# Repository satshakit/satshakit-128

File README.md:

<h1 style="font-family: courier;" align="center"> satshakit 128</h1>
<p align="center">

<div align="center"><i>An improved & fabbable Arduino IDE/libraries compatible board.</i></div>
</p>  

What is satshakit?
--

satshakit is a **Arduino IDE  and libraries compatible**, fabbable and open source board, and also an improved version of [Fabkit](http://fabacademy.org/archives/2015/doc/projects/fabkit-0.4.html). 

Here you can find all of the satshakit boards: **[satshakit organization](https://github.com/satshakit)**.

satshakit 128
--

**satshakit 128** is microcontroller board designed around the **ATMega1284P** chip and it is suitable for complex scenarios in which is needed to have more flash and ram memory, but also the possibility to use 2 serial simultaneously.

In comparison with the other satshakits based on ATMega328P satshakit 128 has:

- **128k** flash memory instead of 32k
- **2 serials** instead of 1
- **16k of ram** instead of 2k
- **32 IO** pins instead of 23

Finally satshakit 128 is smaller than satshakit cnc and it costs **13 euro** each (much less for more).

Here you can have a look on **satshakit 128 board**:

**downloads (right click, download as)**

- [satshakit 128 svg](https://raw.githubusercontent.com/satshakit/satshakit-128/master/media/satshakit128.svg)
- [satshakit 128 internal png](https://raw.githubusercontent.com/satshakit/satshakit-128/master/media/satshakit128_internal.png)
- [satshakit 128 cut png](https://raw.githubusercontent.com/satshakit/satshakit-128/master/media/satshakit128_cut.png)
- [satshakit 128 schematic](https://raw.githubusercontent.com/satshakit/satshakit-128/master/eagle/satshakit128/satshakit128.sch)
- [satshakit 128 board](https://github.com/satshakit/satshakit-128/raw/master/eagle/satshakit128/satshakit128.brd)
- [satshakit 128 BOM Open Document](https://github.com/satshakit/satshakit-128/raw/master/docs/satshakit_128.ods)
- [satshakit 128 BOM Excel](https://github.com/satshakit/satshakit-128/raw/master/docs/satshakit_128.xlsx)

**media**

satshakit 128 uploading bootloader:

satshakit 128 uploading blink:

Getting Started
--
A satshakit board is **very similar to an Arduino board**, thus is possible to use the Arduino IDE and its libraries. When you finish solder satshakit 128, you have to program it. If you want to use satshakit as an Arduino, you first need to **upload Arduino bootloader**. This will also set the ATmega1284P fuses. Before doing any programming you need to **patch your arduino IDE** using a specific set of files that will add the satshakit 128 as an available board to use. 

To add the support for satshakit 128 you can use the **[Mighty 1284P](https://github.com/JChristensen/mighty-1284p/tree/v1.6.3)**, that is provided in this repo inside the **[mighty-1284p folder](https://github.com/satshakit/satshakit-128/tree/master/mighty-1284p)**. 

To do so follow these steps:

1. **download** satshakit 128 repository
2. close **Arduino IDE** before doing anything
3. copy the folder named **mighty-1284p** inside the **Arduino IDE hardware folder**, **arduino-1.6.x/hardware/** in Linux, **Documents/Arduino/hardware** in MacOS 
4. open again the Arduino IDE
5. select **avr-developers.com pinouts 16MHz using Optiboot** board

Now you can use an Arduino as ISP to burn the bootloader and any Arduino sketch you want. To upload a program you connect **Arduino to the satshakit 128** as follows:

Once everything is connected, follow these steps to upload Arduino bootloader:

1. open Arduino IDE 
2. select proper programmer Arduino as ISP
3. select **avr-developers.com pinouts 16MHz using Optiboot** board
4. click on tools->Burn Bootloader

After you burnt the bootloader you can also use an **FTDI usb cable** to program the satshakit 128. Here is the connection schema to program the satshakit 128 using an FTDI cable:

Remember that if you try to program the satshakit 128 using an Arduino, then you will also delete the bootloader, losing the capability to be programmed using the FTDI cable. To hae back this possibility burn again the bootloader.

Here is the Arduino pinout of the satshakit 128:

What's in the repo
--
- **[docs](https://github.com/satshakit/satshakit-128/tree/master/docs)**: BOM files for Farnell
- **[egle projects](https://github.com/satshakit/satshakit-128/tree/master/eagle/satshakit128)**: eagle projects of satshakit
- **[media](https://github.com/satshakit/satshakit-128/tree/master/media)**: svg of satshakits, connections schemas, images for cnc milling machine and fiber laser cutter, other images

Authors
--

- Daniele Ingrassia

Contact
--

- **ingrassiada@gmail.com**
- **[linkedin](http://it.linkedin.com/in/danieleingrassia)**

Thanks
--

[Fablab Kamp-Lintfort](http://fablab.hochschule-rhein-waal.de/index.php/de/)<br />
Hochschule Rhein-Waal<br />
Friedrich-Heinrich-Allee 25, 47475 Kamp-Lintfort, Germany<br />
fablab@hochschule-rhein-waal.de

[Mighty 1284P](https://github.com/JChristensen/mighty-1284p/tree/v1.6.3)

License
--
This work is licensed under the terms of the open source license: Creative Commons Attribution-ShareAlike 4.0 International ([CC BY-SA 4.0](https://creativecommons.org/licenses/by-sa/4.0/)).

Disclaimer  
--

<div class="align-justify">
This hardware/software is provided "as is", and you use the hardware/software at your own risk. Under no circumstances shall any author be liable for direct, indirect, special, incidental, or consequential damages resulting from the use, misuse, or inability to use this hardware/software, even if the authors have been advised of the possibility of such damages.</div>

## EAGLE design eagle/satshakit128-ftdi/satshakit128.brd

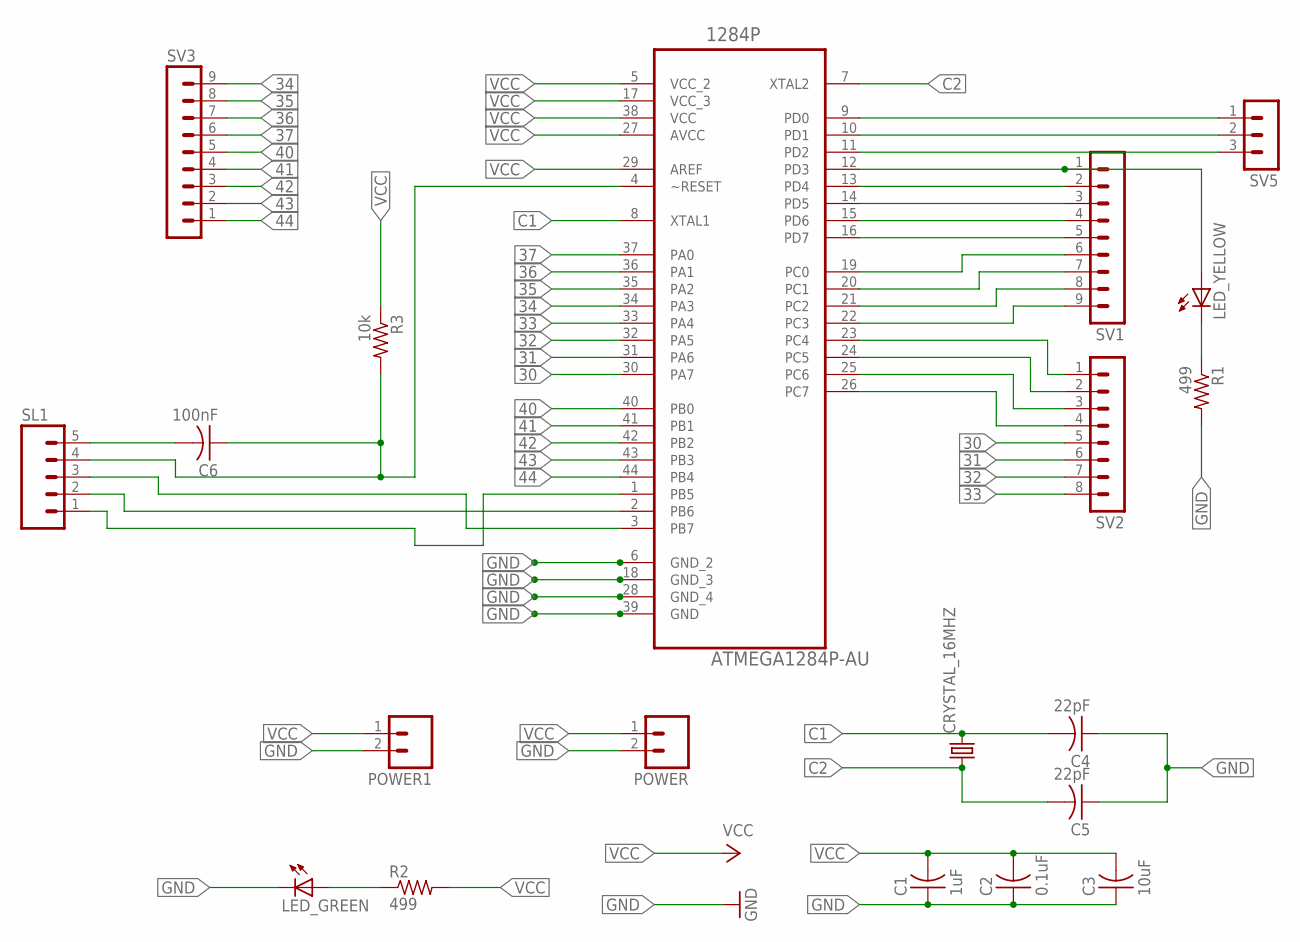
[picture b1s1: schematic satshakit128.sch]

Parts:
1284P: ATMEGA1284P-AU; QFP80P1200X1200X120-44N
C1: 1uF; C1206
C2: 0.1uF; C1206
C3: 10uF; C1206
C4, C5: 22pF; C1206
C6: 100nF; C1206
CRYSTAL_16MHZ: CRYSTALHC49UP; HC49UP
LED_GREEN: LED1206; 1206
LED_YELLOW: LED1206; 1206
POWER, POWER1: M02; 02P
R1, R2: 499; R1206
R3: 10k; R1206
SL1: M05; 05P
SV1, SV3: MA09-1
SV2: MA08-1
SV5: MA03-1

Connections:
30: 1284P.30 (PA7), SV2.5
31: 1284P.31 (PA6), SV2.6
32: 1284P.32 (PA5), SV2.7
33: 1284P.33 (PA4), SV2.8
34: 1284P.34 (PA3), SV3.9
35: 1284P.35 (PA2), SV3.8
36: 1284P.36 (PA1), SV3.7
37: 1284P.37 (PA0), SV3.6
40: 1284P.40 (PB0), SV3.5
41: 1284P.41 (PB1), SV3.4
42: 1284P.42 (PB2), SV3.3
43: 1284P.43 (PB3), SV3.2
44: 1284P.44 (PB4), SV3.1
C1: 1284P.8 (XTAL1), C4.2, CRYSTAL_16MHZ.2
C2: 1284P.7 (XTAL2), C5.2, CRYSTAL_16MHZ.1
GND: 1284P.6 (GND_2), C1.1, C2.1, C3.1, C4.1, C5.1, LED_GREEN.2 (C), POWER.2, POWER1.2, R1.2
unnamed: 1284P.19 (PC0), SV1.6
unnamed: 1284P.20 (PC1), SV1.7
unnamed: 1284P.16 (PD7), SV1.5
unnamed: 1284P.14 (PD5), SV1.3
unnamed: 1284P.13 (PD4), SV1.2
unnamed: 1284P.12 (PD3), LED_YELLOW.1 (A), SV1.1
unnamed: 1284P.11 (PD2), SV5.3
unnamed: 1284P.10 (PD1), SV5.2
unnamed: 1284P.9 (PD0), SV5.1
unnamed: 1284P.21 (PC2), SV1.8
unnamed: 1284P.22 (PC3), SV1.9
unnamed: 1284P.23 (PC4), SV2.1
unnamed: 1284P.24 (PC5), SV2.2
unnamed: 1284P.25 (PC6), SV2.3
unnamed: 1284P.26 (PC7), SV2.4
unnamed: 1284P.15 (PD6), SV1.4
unnamed: 1284P.3 (PB7), SL1.3
unnamed: 1284P.2 (PB6), SL1.2
unnamed: 1284P.1 (PB5), SL1.1
unnamed: 1284P.4 (~RESET), C6.1, R3.2, SL1.4
unnamed: LED_YELLOW.2 (C), R1.1
unnamed: LED_GREEN.1 (A), R2.1
unnamed: C6.2, SL1.5
VCC: 1284P.5 (VCC_2), 1284P.17 (VCC_3), 1284P.27 (AVCC), 1284P.29 (AREF), C1.2, C2.2, C3.2, POWER.1, POWER1.1, R2.2, R3.1

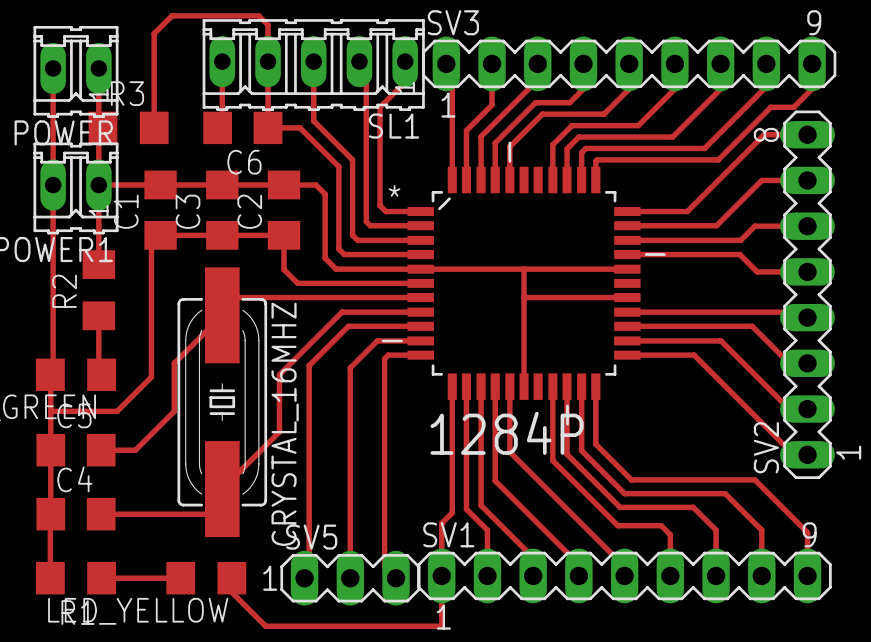
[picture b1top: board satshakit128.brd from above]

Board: 2 copper layers, 20 parts (0 on the bottom side), 40 nets.

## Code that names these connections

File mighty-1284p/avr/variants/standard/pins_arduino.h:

#ifndef Pins_Arduino_h
#define Pins_Arduino_h

#include <avr/pgmspace.h>

// ATMEL ATMEGA1284P
//
//                       +---\/---+
//           (D 0) PB0  1|        |40  PA0 (AI 0 / D24)
//           (D 1) PB1  2|        |39  PA1 (AI 1 / D25)
//      INT2 (D 2) PB2  3|        |38  PA2 (AI 2 / D26)
//       PWM (D 3) PB3  4|        |37  PA3 (AI 3 / D27)
//    PWM/SS (D 4) PB4  5|        |36  PA4 (AI 4 / D28)
//      MOSI (D 5) PB5  6|        |35  PA5 (AI 5 / D29)
//  PWM/MISO (D 6) PB6  7|        |34  PA6 (AI 6 / D30)
//   PWM/SCK (D 7) PB7  8|        |33  PA7 (AI 7 / D31)
//                 RST  9|        |32  AREF
//                 VCC 10|        |31  GND 
//                 GND 11|        |30  AVCC
//               XTAL2 12|        |29  PC7 (D 23)
//               XTAL1 13|        |28  PC6 (D 22)
//      RX0 (D 8)  PD0 14|        |27  PC5 (D 21) TDI
//      TX0 (D 9)  PD1 15|        |26  PC4 (D 20) TDO
// RX1/INT0 (D 10) PD2 16|        |25  PC3 (D 19) TMS
// TX1/INT1 (D 11) PD3 17|        |24  PC2 (D 18) TCK
//      PWM (D 12) PD4 18|        |23  PC1 (D 17) SDA
//      PWM (D 13) PD5 19|        |22  PC0 (D 16) SCL
//      PWM (D 14) PD6 20|        |21  PD7 (D 15) PWM
//                       +--------+
//

/*
   PCINT15-8: D7-0  : bit 1
   PCINT31-24: D15-8  : bit 3
   PCINT23-16: D23-16 : bit 2
   PCINT7-0: D31-24   : bit 0
   */

#define MIGHTY_1284P_VARIANT "STANDARD"

#define NUM_DIGITAL_PINS            32
#define NUM_ANALOG_INPUTS           8
#define analogInputToDigitalPin(p)  ( (p) < NUM_ANALOG_INPUTS ? (p) + 24 : -1 )
#define digitalPinToAnalogPin(p)    ( (p) >= 24 && (p) <= 31 ? (p) - 24 : -1 )
#define analogPinToChannel(p)       ( (p) < NUM_ANALOG_INPUTS ? (p) : (p) >= 24 ? (p) - 24 : -1 )    //required macro for mighty-1284p core
#define digitalPinHasPWM(p)         ( (p) == 3 || (p) == 4 || (p) == 6 || (p) == 7 || (p) == 12 || (p) == 13 || (p) == 14 || (p) == 15 )

static const uint8_t SS   = 4;
static const uint8_t MOSI = 5;
static const uint8_t MISO = 6;
static const uint8_t SCK  = 7;

static const uint8_t SDA = 17;
static const uint8_t SCL = 16;
static const uint8_t LED_BUILTIN = 7;

static const uint8_t A0 = 24;
static const uint8_t A1 = 25;
static const uint8_t A2 = 26;
static const uint8_t A3 = 27;
static const uint8_t A4 = 28;
static const uint8_t A5 = 29;
static const uint8_t A6 = 30;
static const uint8_t A7 = 31;

#define digitalPinToPCICR(p)    ( (p) >= 0 && (p) < NUM_DIGITAL_PINS ? &PCICR : (uint8_t *)0 )
#define digitalPinToPCICRbit(p) ( (p) <= 7 ? 1 : (p) <= 15 ? 3 : (p) <= 23 ? 2 : 0 )
#define digitalPinToPCMSK(p)    ( (p) <= 7 ? &PCMSK1 : (p) <= 15 ? &PCMSK3 : (p) <= 23 ? &PCMSK2 : &PCMSK0 )
#define digitalPinToPCMSKbit(p) ( (p) % 8 )
// return associated INTx number for associated/valid pins,
// otherwise NOT_AN_INTERRUPT
#define digitalPinToInterrupt(p) \
	(\
	(p) == 10 ? 0 : \
	(p) == 11 ? 1 : \
	(p) == 2 ? 2 : \
	NOT_AN_INTERRUPT)


#define PA 1
#define PB 2
#define PC 3
#define PD 4

// specify port for each pin D0-D31
#define PORT_D0 PB
#define PORT_D1 PB
#define PORT_D2 PB
#define PORT_D3 PB
#define PORT_D4 PB
#define PORT_D5 PB
#define PORT_D6 PB
#define PORT_D7 PB
#define PORT_D8 PD
#define PORT_D9 PD
#define PORT_D10 PD
#define PORT_D11 PD
#define PORT_D12 PD
#define PORT_D13 PD
#define PORT_D14 PD
#define PORT_D15 PD
#define PORT_D16 PC
#define PORT_D17 PC
#define PORT_D18 PC
#define PORT_D19 PC
#define PORT_D20 PC
#define PORT_D21 PC
#define PORT_D22 PC
#define PORT_D23 PC
#define PORT_D24 PA
#define PORT_D25 PA
#define PORT_D26 PA
#define PORT_D27 PA
#define PORT_D28 PA
#define PORT_D29 PA
#define PORT_D30 PA
#define PORT_D31 PA

// specify port bit for each pin D0-D31
#define BIT_D0 0
#define BIT_D1 1
#define BIT_D2 2
#define BIT_D3 3
#define BIT_D4 4
#define BIT_D5 5
#define BIT_D6 6
#define BIT_D7 7
#define BIT_D8 0
#define BIT_D9 1
#define BIT_D10 2
#define BIT_D11 3
#define BIT_D12 4
#define BIT_D13 5
#define BIT_D14 6
#define BIT_D15 7
#define BIT_D16 0
#define BIT_D17 1
#define BIT_D18 2
#define BIT_D19 3
#define BIT_D20 4
#define BIT_D21 5
#define BIT_D22 6
#define BIT_D23 7
#define BIT_D24 0
#define BIT_D25 1
#define BIT_D26 2
#define BIT_D27 3
#define BIT_D28 4
#define BIT_D29 5
#define BIT_D30 6
#define BIT_D31 7

// macro equivalents of PROGMEM arrays port_to_mode_PGM[] etc. below
#define PORT_TO_MODE(x) (x == 1 ? &DDRA : (x == 2 ? &DDRB : (x == 3 ? &DDRC : (x == 4 ? &DDRD : NOT_A_PORT)))) 
#define PORT_TO_OUTPUT(x) (x == 1 ? &PORTA : (x == 2 ? &PORTB : (x == 3 ? &PORTC : (x == 4 ? &PORTD : NOT_A_PORT))))
#define PORT_TO_INPUT(x) (x == 1 ? &PINA : (x == 2 ? &PINB : (x == 3 ? &PINC : (x == 4 ? &PIND : NOT_A_PORT)))) 
 
#ifdef ARDUINO_MAIN
// these arrays map port names (e.g. port B) to the
// appropriate addresses for various functions (e.g. reading
// and writing)
const uint16_t PROGMEM port_to_mode_PGM[] =
{
  NOT_A_PORT,
  (uint16_t) &DDRA,
  (uint16_t) &DDRB,
  (uint16_t) &DDRC,
  (uint16_t) &DDRD,
};

const uint16_t PROGMEM port_to_output_PGM[] =
{
  NOT_A_PORT,
  (uint16_t) &PORTA,
  (uint16_t) &PORTB,
  (uint16_t) &PORTC,
  (uint16_t) &PORTD,
};

const uint16_t PROGMEM port_to_input_PGM[] =
{
  NOT_A_PORT,
  (uint16_t) &PINA,
  (uint16_t) &PINB,
  (uint16_t) &PINC,
  (uint16_t) &PIND,
};

const uint8_t PROGMEM digital_pin_to_port_PGM[NUM_DIGITAL_PINS] =
{
  PORT_D0,
  PORT_D1,
  PORT_D2,
  PORT_D3,
  PORT_D4,
  PORT_D5,
  PORT_D6,
  PORT_D7,
  PORT_D8,
  PORT_D9,
  PORT_D10,
  PORT_D11,
  PORT_D12,
  PORT_D13,
  PORT_D14,
  PORT_D15,
  PORT_D16,
  PORT_D17,
  PORT_D18,
  PORT_D19,
  PORT_D20,
  PORT_D21,
  PORT_D22,
  PORT_D23,
  PORT_D24,
  PORT_D25,
  PORT_D26,
  PORT_D27,
  PORT_D28,
  PORT_D29,
  PORT_D30,
  PORT_D31
};

const uint8_t PROGMEM digital_pin_to_bit_mask_PGM[NUM_DIGITAL_PINS] =
{
  _BV(BIT_D0),
  _BV(BIT_D1),
  _BV(BIT_D2),
  _BV(BIT_D3),
  _BV(BIT_D4),
  _BV(BIT_D5),
  _BV(BIT_D6),
  _BV(BIT_D7),
  _BV(BIT_D8),
  _BV(BIT_D9),
  _BV(BIT_D10),
  _BV(BIT_D11),
  _BV(BIT_D12),
  _BV(BIT_D13),
  _BV(BIT_D14),
  _BV(BIT_D15),
  _BV(BIT_D16),
  _BV(BIT_D17),
  _BV(BIT_D18),
  _BV(BIT_D19),
  _BV(BIT_D20),
  _BV(BIT_D21),
  _BV(BIT_D22),
  _BV(BIT_D23),
  _BV(BIT_D24),
  _BV(BIT_D25),
  _BV(BIT_D26),
  _BV(BIT_D27),
  _BV(BIT_D28),
  _BV(BIT_D29),
  _BV(BIT_D30),
  _BV(BIT_D31)
};

const uint8_t PROGMEM digital_pin_to_timer_PGM[] =
{
  NOT_ON_TIMER, /* 0  - PB0 */
  NOT_ON_TIMER, /* 1  - PB1 */
  NOT_ON_TIMER, /* 2  - PB2 */
  TIMER0A,     	/* 3  - PB3 */
  TIMER0B, 	/* 4  - PB4 */
  NOT_ON_TIMER, /* 5  - PB5 */
  TIMER3A, 	/* 6  - PB6 */
  TIMER3B,	/* 7  - PB7 */
  NOT_ON_TIMER, /* 8  - PD0 */
  NOT_ON_TIMER, /* 9  - PD1 */
  NOT_ON_TIMER, /* 10 - PD2 */
  NOT_ON_TIMER, /* 11 - PD3 */
  TIMER1B,     	/* 12 - PD4 */
  TIMER1A,     	/* 13 - PD5 */
  TIMER2B,     	/* 14 - PD6 */
  TIMER2A,     	/* 15 - PD7 */
  NOT_ON_TIMER, /* 16 - PC0 */
  NOT_ON_TIMER, /* 17 - PC1 */
  NOT_ON_TIMER, /* 18 - PC2 */
  NOT_ON_TIMER, /* 19 - PC3 */
  NOT_ON_TIMER, /* 20 - PC4 */
  NOT_ON_TIMER, /* 21 - PC5 */
  NOT_ON_TIMER, /* 22 - PC6 */
  NOT_ON_TIMER, /* 23 - PC7 */
  NOT_ON_TIMER, /* 24 - PA0 */
  NOT_ON_TIMER, /* 25 - PA1 */
  NOT_ON_TIMER, /* 26 - PA2 */
  NOT_ON_TIMER, /* 27 - PA3 */
  NOT_ON_TIMER, /* 28 - PA4 */
  NOT_ON_TIMER, /* 29 - PA5 */
  NOT_ON_TIMER, /* 30 - PA6 */
  NOT_ON_TIMER  /* 31 - PA7 */
};

#endif // ARDUINO_MAIN

#endif // Pins_Arduino_h
// vim:ai:cin:sts=2 sw=2 ft=cpp

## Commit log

2016-05-31 first satshakit128 commit
2016-05-31 added satshakites
2016-06-01 added documentation
2016-06-03 fixed pinout error
2016-07-02 added a new version that is possible to proigram using only the FTDI
2016-07-02 added the pngs for the new version
2017-01-22 added the 2nd reset pin to enable the FTDI programming
2017-01-22 fixed link to ftdi programming
2017-01-22 added license file
2017-01-22 removed the satshakit boards list
2017-10-17 change license file formatting
2020-05-31 license change
